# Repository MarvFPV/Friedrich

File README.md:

# Friedrich
50% 3D printed keyboard designed to be printable on regular sized 3d printers.

This place is designed to be 3d printed with a regular FDM printer, beware of that when ordering it from any other material. 

To make the case printable on regular machines, i had to cut it in half. To fuse those halves together you can either use super glue or melt them together by running a (clean) soldering iron tip through the seam (my preferred way). Make sure to re-tin your soldering iron afterwards tho as this process may damage your tip.

## Required components for handwires
* 52 MX style switches
* 2 2u MX platemount stabs
* 1 6.25u MX platemount stab
* 52 Diodes
* a Promicro
* one of ai03's [unified daughterboards](https://github.com/ai03-2725/Unified-Daughterboard)
* a few cables to wire up the matrix
* 4 m3x6mm screws
* 6 m3x8mm countersunk screws

I personally tend to remove the microUSB connector from the Promicro and solder it directly to a unified daughterboard, that's also why the Promicro cutout may not fit with the USB connector still on the PCB. (I should really write up some documentation on that ^^)

## PCB version
The PCB is not yet compatible with the switch plate in the repo, some cutting / melting away will have to be done to get it to fit with PCBmount stabs. Or just annoy me to add it ^^

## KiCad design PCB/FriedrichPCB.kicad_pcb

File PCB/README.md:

# Friedrich PCB

[![CC BY-NC-SA 4.0][cc-by-nc-sa-shield]][cc-by-nc-sa]

### Atmega32u4 based PCB for the Friedrich50 keyboard

---

[LCSC BOM](FriedrichPCB.csv)

[JLC CPL](FriedrichPCB_cpl_jlc.csv)

[JST connector for USB](https://www.digikey.de/product-detail/en/jst-sales-america-inc/SM04B-SRSS-TB-LF-SN/455-1804-1-ND/926875)

---

This work is licensed under a
[Creative Commons Attribution-NonCommercial-ShareAlike 4.0 International License][cc-by-nc-sa].

[![CC BY-NC-SA 4.0][cc-by-nc-sa-image]][cc-by-nc-sa]

[cc-by-nc-sa]: http://creativecommons.org/licenses/by-nc-sa/4.0/
[cc-by-nc-sa-image]: https://licensebuttons.net/l/by-nc-sa/4.0/88x31.png
[cc-by-nc-sa-shield]: https://img.shields.io/badge/License-CC%20BY--NC--SA%204.0-lightgrey.svg

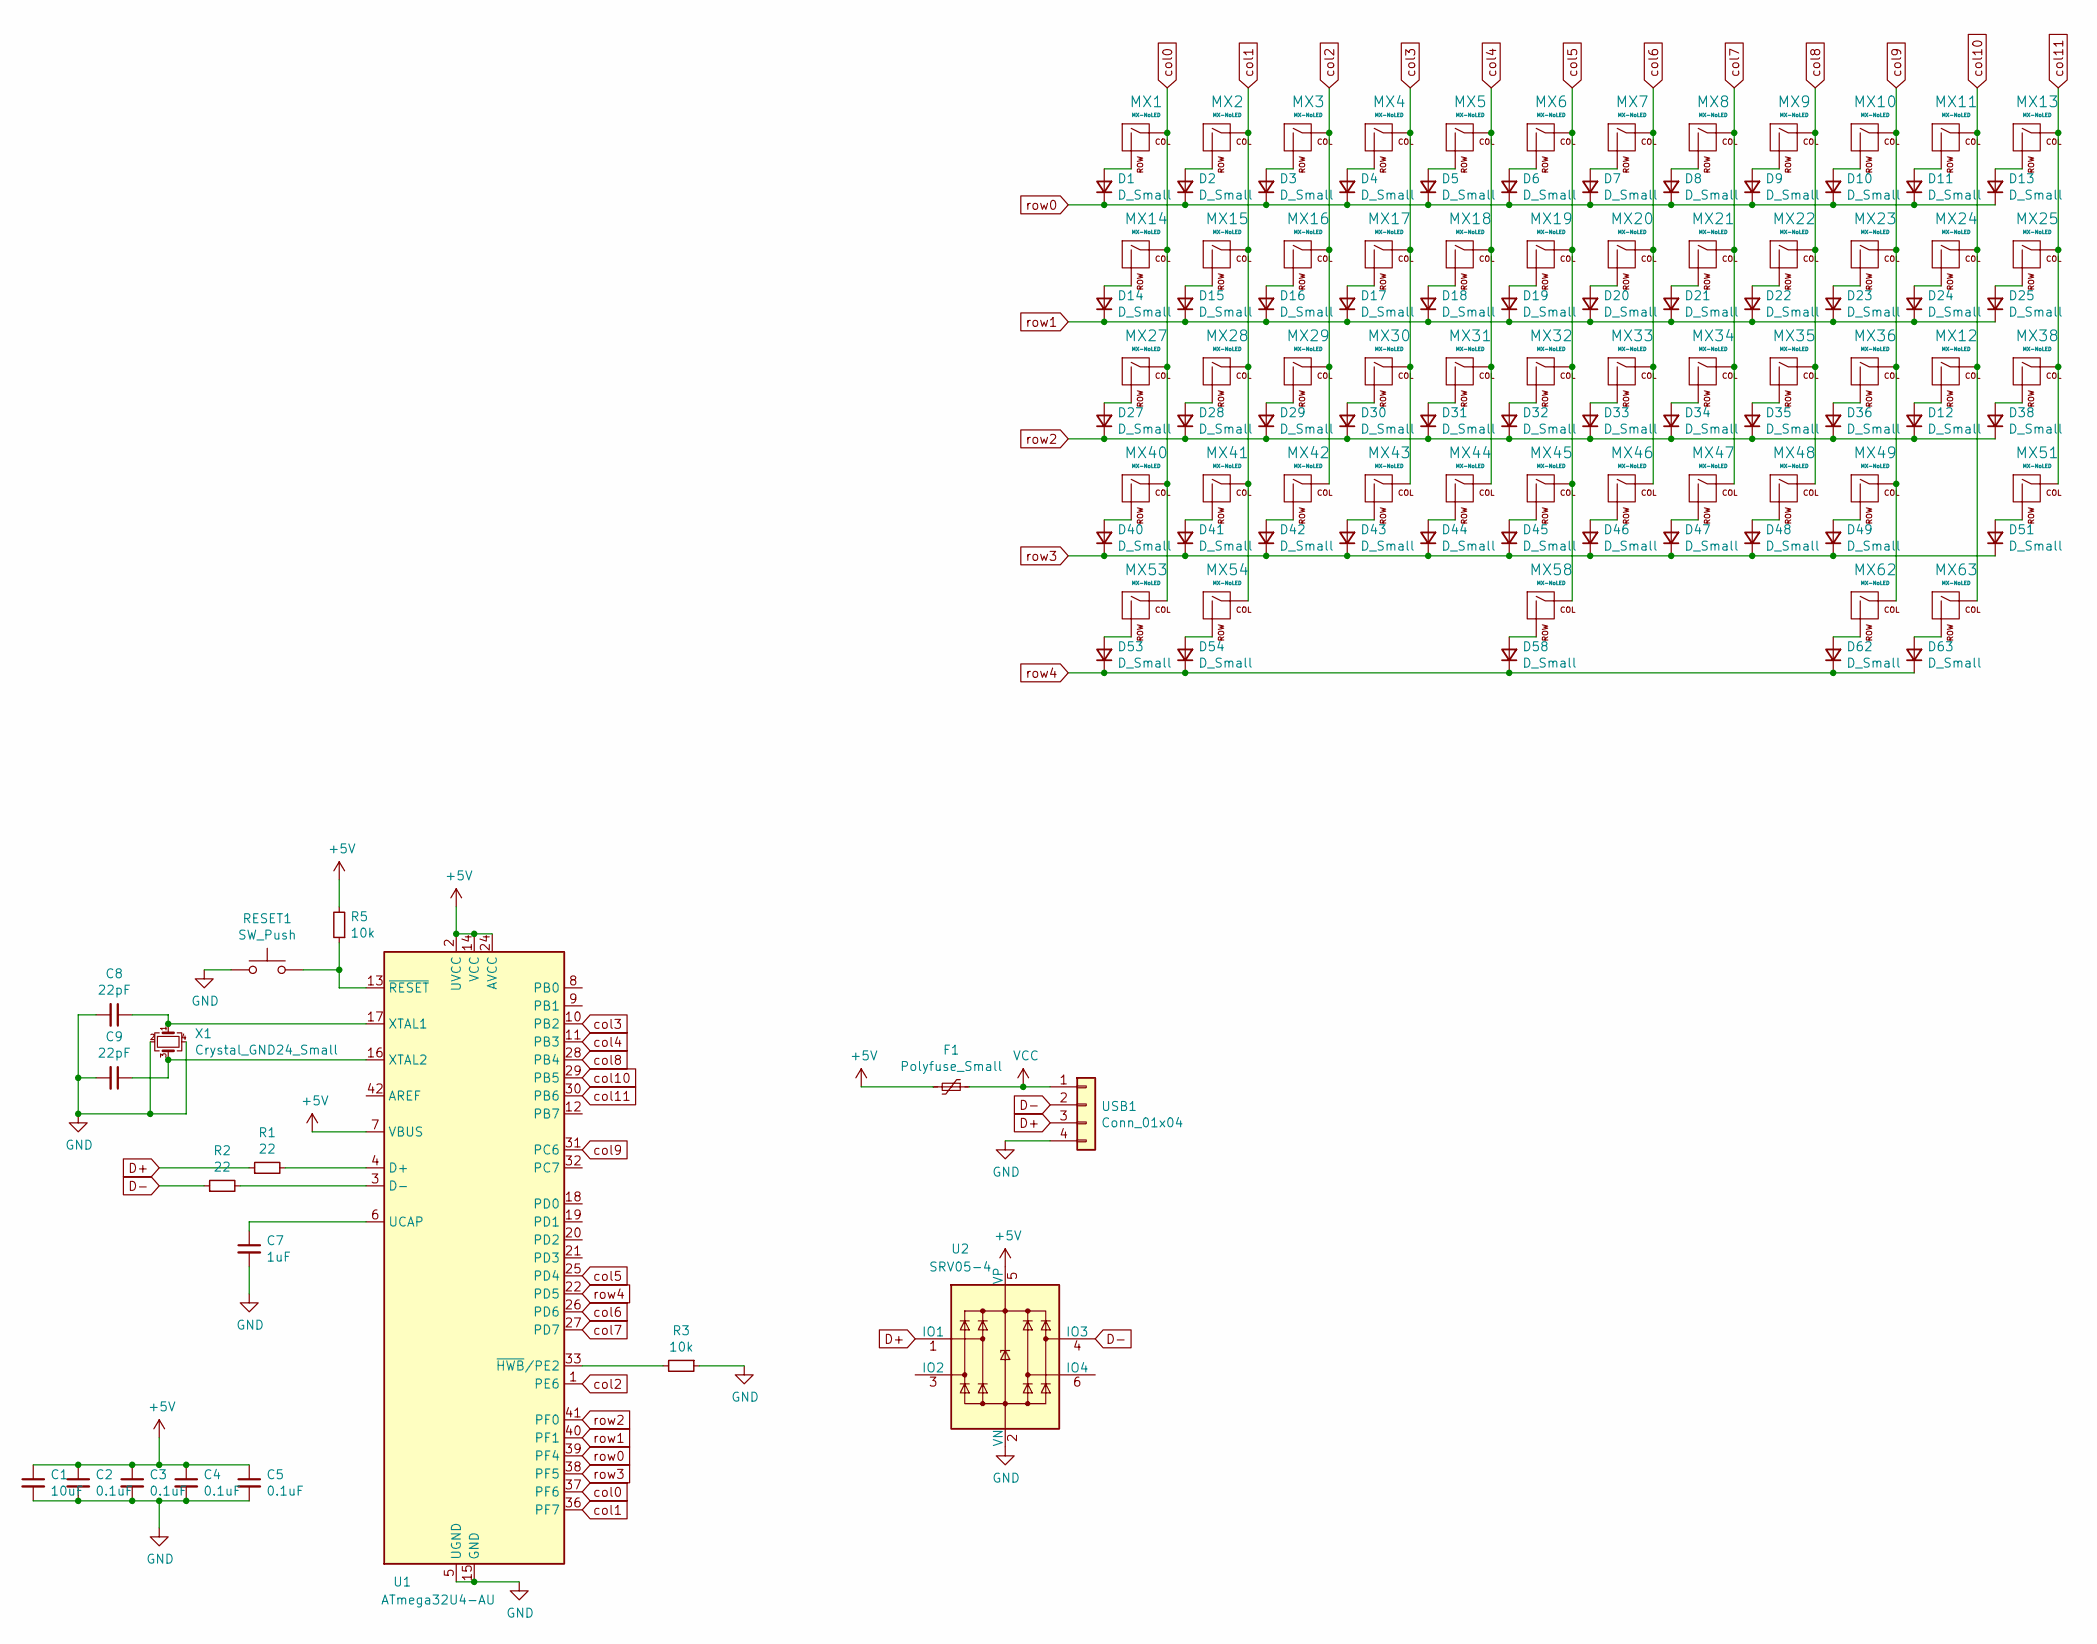
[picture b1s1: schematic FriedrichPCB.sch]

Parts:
C1: 10uF; C_0805_2012Metric; LCSC C91245
C2, C3, C4, C5: 0.1uF; C_0805_2012Metric; LCSC C49678
C7: 1uF; C_0805_2012Metric; LCSC C28323
C8, C9: 22pF; C_0805_2012Metric; LCSC C1804
D1, D2, D3, D4, D5, D6, D7, D8, D9, D10, D11, D12, D13, D14, D15, D16, D17, D18, D19, D20, D21, D22, D23, D24, D25, D27, D28, D29, D30, D31, D32, D33, D34, D35, D36, D38, D40, D41, D42, D43, D44, D45, D46, D47, D48, D49, D51, D53, D54, D58, D62, D63: D_Small; D_SOD-123; LCSC C81598
F1: Polyfuse_Small; Fuse_1206_3216Metric; LCSC C163133
MX1, MX2, MX3, MX4, MX5, MX6, MX7, MX8, MX9, MX10, MX11, MX12, MX13, MX15, MX16, MX17, MX18, MX19, MX20, MX21, MX22, MX23, MX24, MX28, MX29, MX30, MX31, MX32, MX33, MX34, MX35, MX36, MX41, MX42, MX43, MX44, MX45, MX46, MX47, MX48, MX49, MX53, MX63: MX-NoLED; MXOnly-1U-NoLED
MX14, MX25: MX-NoLED; MXOnly-1.5U-NoLED
MX27, MX51: MX-NoLED; MXOnly-1.75U-NoLED
MX38: MX-NoLED; MXOnly-2.25U-NoLED
MX40: MX-NoLED; MXOnly-2.25U-ReversedStabilizers-NoLED
MX54, MX62: MX-NoLED; MXOnly-1.25U-NoLED
MX58: MX-NoLED; MXOnly-6.25U-ReversedStabilizers-NoLED
R1, R2: 22; R_0805_2012Metric; LCSC C17561
R3, R5: 10k; R_0805_2012Metric; LCSC C17414
RESET1: SW_Push; SW_SPST_TL3342; LCSC C318884
U1: ATmega32U4-AU; TQFP-44_10x10mm_P0.8mm; LCSC C44854
U2: SRV05-4; SOT-23-6; LCSC C85364
USB1: Conn_01x04; JST_SH_SM04B-SRSS-TB_1x04-1MP_P1.00mm_Horizontal
X1: Crystal_GND24_Small; Crystal_SMD_3225-4Pin_3.2x2.5mm; LCSC C13738

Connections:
+5V: C1.1, C2.1, C3.1, C4.1, C5.1, F1.2, R5.2, U1.2 (UVCC), U1.7 (VBUS), U1.14 (VCC), U1.24 (AVCC), U1.34 (VCC), U1.44 (AVCC), U2.5 (VP)
D+: R1.1, U2.1 (IO1), USB1.3
D-: R2.1, U2.4 (IO3), USB1.2
GND: C1.2, C2.2, C3.2, C4.2, C5.2, C7.2, C8.2, C9.2, R3.1, RESET1.1, U1.5 (UGND), U1.15 (GND), U1.23 (GND), U1.35 (GND), U1.43 (GND), U2.2 (VN), USB1.4, X1.2, X1.4; also elsewhere on the board
unnamed: C7.1, U1.6 (UCAP)
unnamed: C8.1, U1.17 (XTAL1), X1.1
unnamed: C9.1, U1.16 (XTAL2), X1.3
unnamed: D1.2 (A), MX1.2 (ROW)
unnamed: D2.2 (A), MX2.2 (ROW)
unnamed: D3.2 (A), MX3.2 (ROW)
unnamed: D4.2 (A), MX4.2 (ROW)
unnamed: D5.2 (A), MX5.2 (ROW)
unnamed: D6.2 (A), MX6.2 (ROW)
unnamed: D7.2 (A), MX7.2 (ROW)
unnamed: D8.2 (A), MX8.2 (ROW)
unnamed: D9.2 (A), MX9.2 (ROW)
unnamed: D10.2 (A), MX10.2 (ROW)
unnamed: D11.2 (A), MX11.2 (ROW)
unnamed: D12.2 (A), MX12.2 (ROW)
unnamed: D13.2 (A), MX13.2 (ROW)
unnamed: D14.2 (A), MX14.2 (ROW)
unnamed: D15.2 (A), MX15.2 (ROW)
unnamed: D16.2 (A), MX16.2 (ROW)
unnamed: D17.2 (A), MX17.2 (ROW)
unnamed: D18.2 (A), MX18.2 (ROW)
unnamed: D19.2 (A), MX19.2 (ROW)
unnamed: D20.2 (A), MX20.2 (ROW)
unnamed: D21.2 (A), MX21.2 (ROW)
unnamed: D22.2 (A), MX22.2 (ROW)
unnamed: D23.2 (A), MX23.2 (ROW)
unnamed: D24.2 (A), MX24.2 (ROW)
unnamed: D25.2 (A), MX25.2 (ROW)
unnamed: D27.2 (A), MX27.2 (ROW)
unnamed: D28.2 (A), MX28.2 (ROW)
unnamed: D29.2 (A), MX29.2 (ROW)
unnamed: D30.2 (A), MX30.2 (ROW)
unnamed: D31.2 (A), MX31.2 (ROW)
unnamed: D32.2 (A), MX32.2 (ROW)
unnamed: D33.2 (A), MX33.2 (ROW)
unnamed: D34.2 (A), MX34.2 (ROW)
unnamed: D35.2 (A), MX35.2 (ROW)
unnamed: D36.2 (A), MX36.2 (ROW)
unnamed: D38.2 (A), MX38.2 (ROW)
unnamed: D40.2 (A), MX40.2 (ROW)
unnamed: D41.2 (A), MX41.2 (ROW)
unnamed: D42.2 (A), MX42.2 (ROW)
unnamed: D43.2 (A), MX43.2 (ROW)
unnamed: D44.2 (A), MX44.2 (ROW)
unnamed: D45.2 (A), MX45.2 (ROW)
unnamed: D46.2 (A), MX46.2 (ROW)
unnamed: D47.2 (A), MX47.2 (ROW)
unnamed: D48.2 (A), MX48.2 (ROW)
unnamed: D49.2 (A), MX49.2 (ROW)
unnamed: D51.2 (A), MX51.2 (ROW)
unnamed: D53.2 (A), MX53.2 (ROW)
unnamed: D54.2 (A), MX54.2 (ROW)
unnamed: D58.2 (A), MX58.2 (ROW)
unnamed: D62.2 (A), MX62.2 (ROW)
unnamed: D63.2 (A), MX63.2 (ROW)
unnamed: R1.2, U1.4 (D+)
unnamed: R2.2, U1.3 (D-)
unnamed: R3.2, U1.33 (~HWB~/PE2)
unnamed 62: R5.1, RESET1.2, U1.13 (~RESET); also elsewhere on the board
VCC: F1.1, USB1.1
col0: MX1.1 (COL), MX14.1 (COL), MX27.1 (COL), MX40.1 (COL), MX53.1 (COL), U1.37 (PF6)
col1: MX2.1 (COL), MX15.1 (COL), MX28.1 (COL), MX41.1 (COL), MX54.1 (COL), U1.36 (PF7)
col2: MX3.1 (COL), MX16.1 (COL), MX29.1 (COL), MX42.1 (COL), U1.1 (PE6)
col3: MX4.1 (COL), MX17.1 (COL), MX30.1 (COL), MX43.1 (COL), U1.10 (PB2)
col4: MX5.1 (COL), MX18.1 (COL), MX31.1 (COL), MX44.1 (COL), U1.11 (PB3)
col5: MX6.1 (COL), MX19.1 (COL), MX32.1 (COL), MX45.1 (COL), MX58.1 (COL), U1.25 (PD4)
col6: MX7.1 (COL), MX20.1 (COL), MX33.1 (COL), MX46.1 (COL), U1.26 (PD6)
col7: MX8.1 (COL), MX21.1 (COL), MX34.1 (COL), MX47.1 (COL), U1.27 (PD7)
col8: MX9.1 (COL), MX22.1 (COL), MX35.1 (COL), MX48.1 (COL), U1.28 (PB4)
col9: MX10.1 (COL), MX23.1 (COL), MX36.1 (COL), MX49.1 (COL), MX62.1 (COL), U1.31 (PC6)
col10: MX11.1 (COL), MX12.1 (COL), MX24.1 (COL), MX63.1 (COL), U1.29 (PB5)
col11: MX13.1 (COL), MX25.1 (COL), MX38.1 (COL), MX51.1 (COL), U1.30 (PB6)
row0: D1.1 (K), D2.1 (K), D3.1 (K), D4.1 (K), D5.1 (K), D6.1 (K), D7.1 (K), D8.1 (K), D9.1 (K), D10.1 (K), D11.1 (K), D13.1 (K), U1.39 (PF4)
row1: D14.1 (K), D15.1 (K), D16.1 (K), D17.1 (K), D18.1 (K), D19.1 (K), D20.1 (K), D21.1 (K), D22.1 (K), D23.1 (K), D24.1 (K), D25.1 (K), U1.40 (PF1)
row2: D12.1 (K), D27.1 (K), D28.1 (K), D29.1 (K), D30.1 (K), D31.1 (K), D32.1 (K), D33.1 (K), D34.1 (K), D35.1 (K), D36.1 (K), D38.1 (K), U1.41 (PF0)
row3: D40.1 (K), D41.1 (K), D42.1 (K), D43.1 (K), D44.1 (K), D45.1 (K), D46.1 (K), D47.1 (K), D48.1 (K), D49.1 (K), D51.1 (K), U1.38 (PF5)
row4: D53.1 (K), D54.1 (K), D58.1 (K), D62.1 (K), D63.1 (K), U1.22 (PD5)

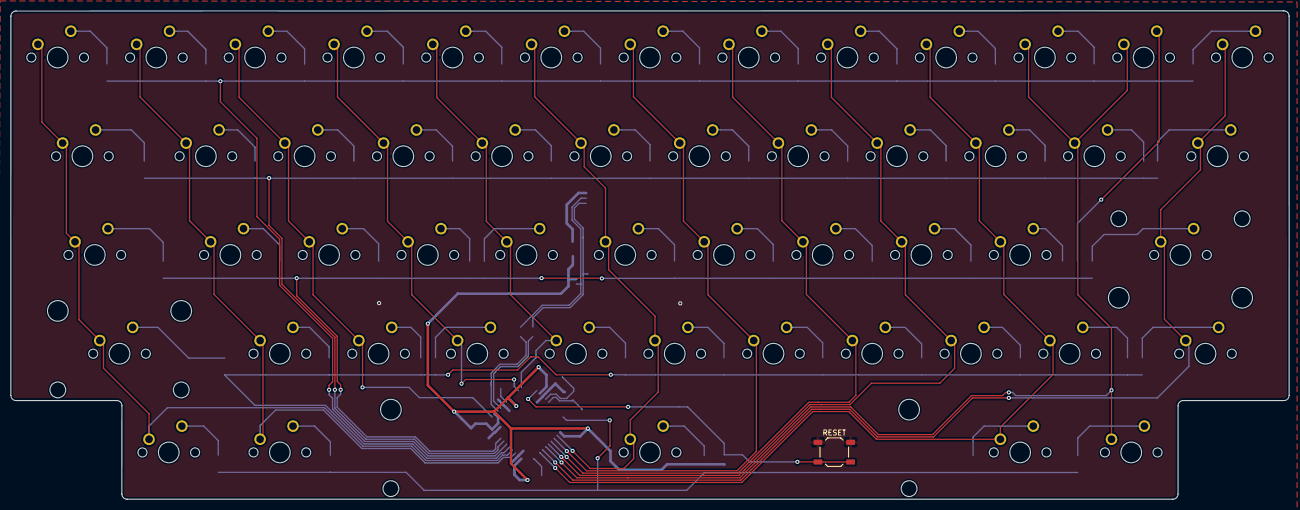
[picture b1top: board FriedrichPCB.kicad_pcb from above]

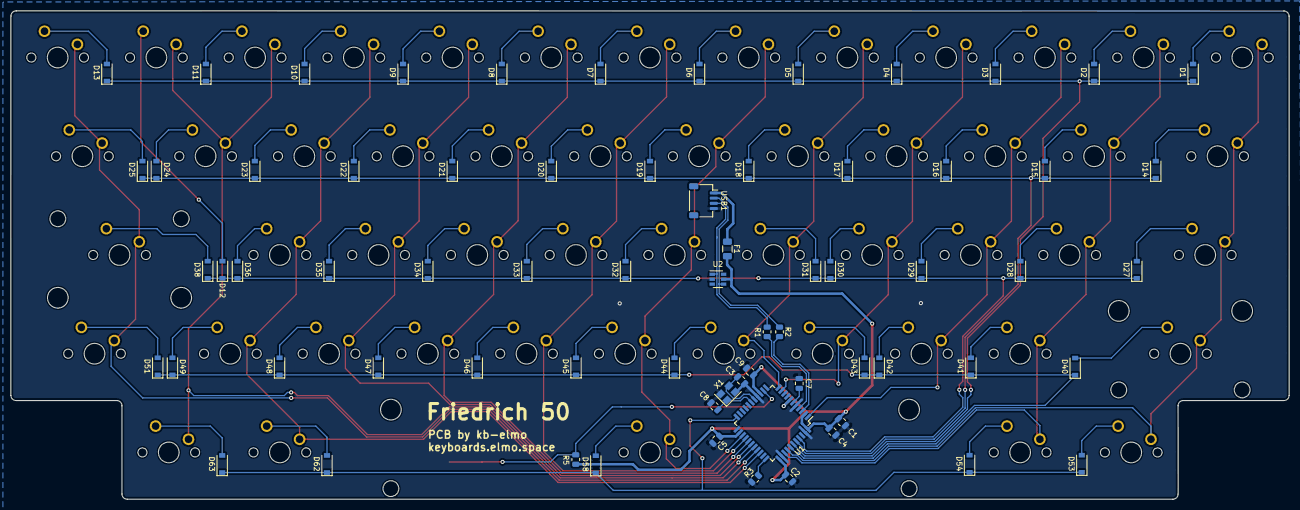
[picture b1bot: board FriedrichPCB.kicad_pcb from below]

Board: 2 copper layers, 246.7 x 94.2 mm, 122 parts (69 on the bottom side), 81 nets.

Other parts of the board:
RESET: SW_Push; SW_SPST_TL3342

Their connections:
GND: RESET.1; also elsewhere on the board
unnamed 62: RESET.2; also elsewhere on the board

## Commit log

2021-01-24 Added 3D files
2021-01-25 add PCB
2021-08-19 Create LICENSE
